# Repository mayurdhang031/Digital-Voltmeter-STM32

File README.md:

# Digital Voltmeter using STM32

## Overview
A digital voltmeter PCB designed using KiCad and based on the STM32 microcontroller. The system measures DC voltage and displays the measured value in real time.

## Features
- STM32 Microcontroller
- DC Voltage Measurement
- KiCad PCB Design
- 2-Layer PCB
- Embedded C Firmware

## Software Used
- KiCad
- STM32CubeIDE
- Embedded C

## Hardware
- STM32 Microcontroller
- Voltage Divider Circuit
- Resistors
- Capacitors
- Crystal Oscillator
- Power Supply

## Repository Contents
- Schematic (.kicad_sch)
- PCB Layout (.kicad_pcb)
- KiCad Project (.kicad_pro)

## Images
- PCB Layout
- 3D PCB View
- Schematic

## Author
Mayur Dhang

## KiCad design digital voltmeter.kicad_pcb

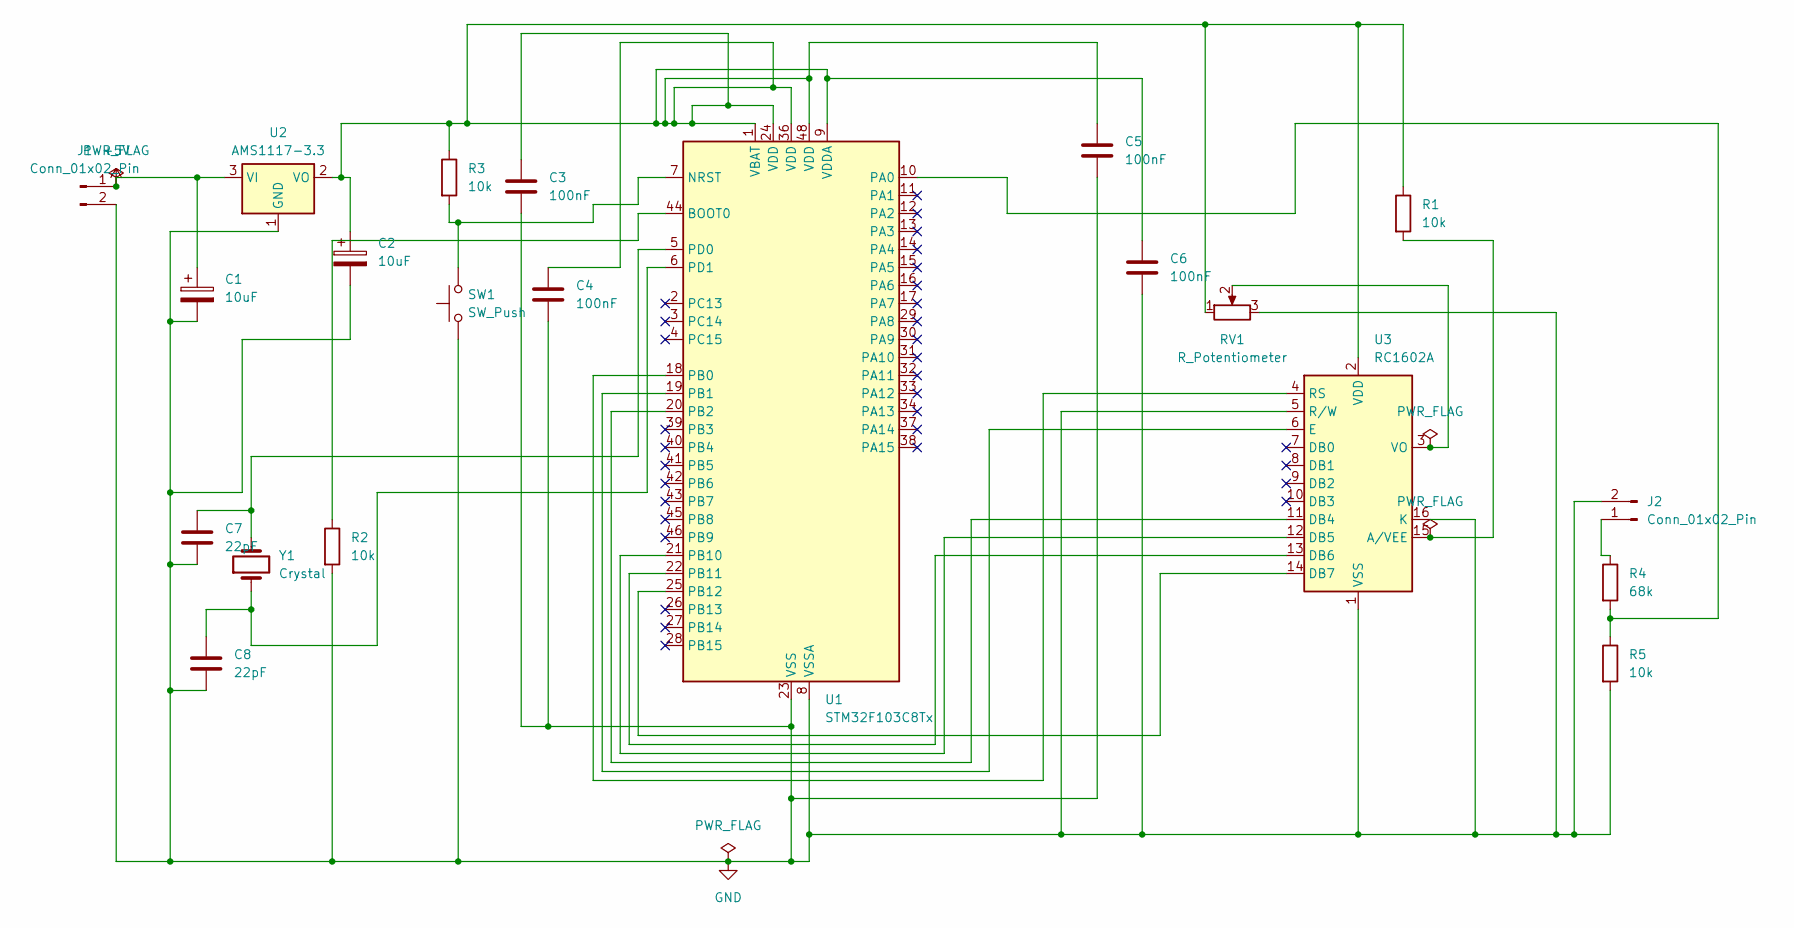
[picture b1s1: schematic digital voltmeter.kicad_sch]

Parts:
C1, C2: 10uF; CP_Radial_D5.0mm_P2.00mm
C3, C4, C5, C6: 100nF; C_Disc_D5.0mm_W2.5mm_P5.00mm
C7, C8: 22pF; C_Disc_D5.0mm_W2.5mm_P5.00mm
J1, J2: Conn_01x02_Pin; PinHeader_1x02_P2.54mm_Vertical
R1, R2, R3, R5: 10k; R_Axial_DIN0207_L6.3mm_D2.5mm_P7.62mm_Horizontal
R4: 68k; R_Axial_DIN0207_L6.3mm_D2.5mm_P7.62mm_Horizontal
RV1: R_Potentiometer; Potentiometer_Bourns_3296W_Vertical
SW1: SW_Push; SW_PUSH_6mm
U1: STM32F103C8Tx; LQFP-48_7x7mm_P0.5mm
U2: AMS1117-3.3; SOT-223-3_TabPin2
U3: RC1602A
Y1: Crystal; Crystal_HC49-U_Vertical

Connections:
+5V: C1.1, J1.1, U2.3 (VI)
GND: C1.2, C2.2, C3.2, C4.2, C5.2, C6.2, C7.2, C8.2, J1.2, J2.2, R2.2, R5.2, RV1.3, SW1.1, U1.8 (VSSA), U1.23 (VSS), U1.35 (VSS), U1.47 (VSS), U2.1 (GND), U3.1 (VSS), U3.5 (R/W), U3.16 (K)
unnamed: J2.1, R4.1
unnamed: R2.1, U1.44 (BOOT0)
unnamed: R3.2, SW1.2, U1.7 (NRST)
unnamed: R4.2, R5.1, U1.10 (PA0)
unnamed: U1.18 (PB0), U3.4 (RS)
unnamed: U1.19 (PB1), U3.6 (E)
unnamed: U1.20 (PB2), U3.11 (DB4)
unnamed: U1.21 (PB10), U3.12 (DB5)
unnamed: U1.22 (PB11), U3.13 (DB6)
unnamed: U1.25 (PB12), U3.14 (DB7)
unnamed: C7.1, U1.5 (PD0), Y1.2
unnamed: C8.1, U1.6 (PD1), Y1.1
unnamed: C2.1, C3.1, C4.1, C5.1, C6.1, R1.1, R3.1, RV1.1, U1.1 (VBAT), U1.9 (VDDA), U1.24 (VDD), U1.36 (VDD), U1.48 (VDD), U2.2 (VO), U3.2 (VDD)
unnamed: R1.2, U3.15 (A/VEE)
unnamed: RV1.2, U3.3 (VO)

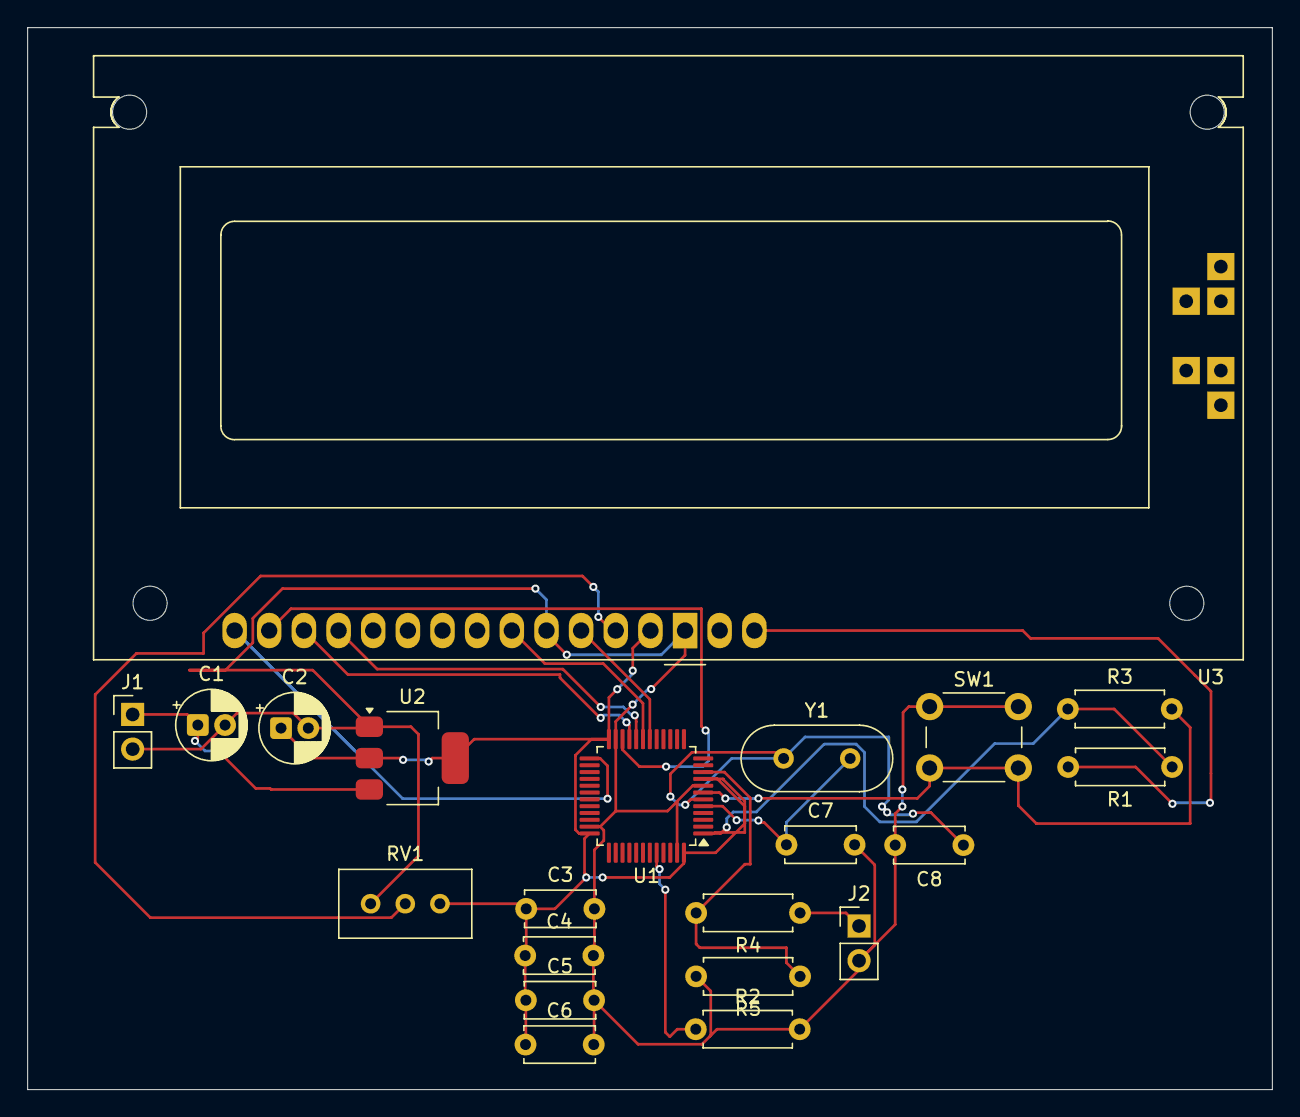
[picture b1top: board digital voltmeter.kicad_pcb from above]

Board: 2 copper layers, 91.2 x 77.8 mm, 21 parts (0 on the bottom side), 17 nets.
